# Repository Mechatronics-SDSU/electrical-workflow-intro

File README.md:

This system takes in an input A-F to change the brightness of an LED. This LED is also controlled by a button. When the button is pressed it turns the LED on, when the button is pressed again it turns the LED off. This is done on a high level by creating two circuits using an arduino and a breadboard, the button uses a pull-down resistor to guarantee a more precise output. After the button is pressed it switches the pin for the LED on which lights it up. On a low level, it uses the ATmega328P as a power supply and pin outputs, this goes through the tracks to interact with other parts of the board to function similarly to what was stated above.

The main challenges faced were learning how to create a proper schematic to make the PCB and learning how to create the basic circuit needed for the tinkercad simulation to run properly. I fixed most of this by finding guides online on what steps I needed to take to make it properly. This was overall a challenge but I learned a lot, the high level simulation works as expected and the PCB clears all design checks.

The parts used to make the board were a SPST button, an LED, an ATmega328P-A, two 10k ohm resistors, one 330 ohm resistor, the AVR-ISP-6, two capacitors, and a crystal.

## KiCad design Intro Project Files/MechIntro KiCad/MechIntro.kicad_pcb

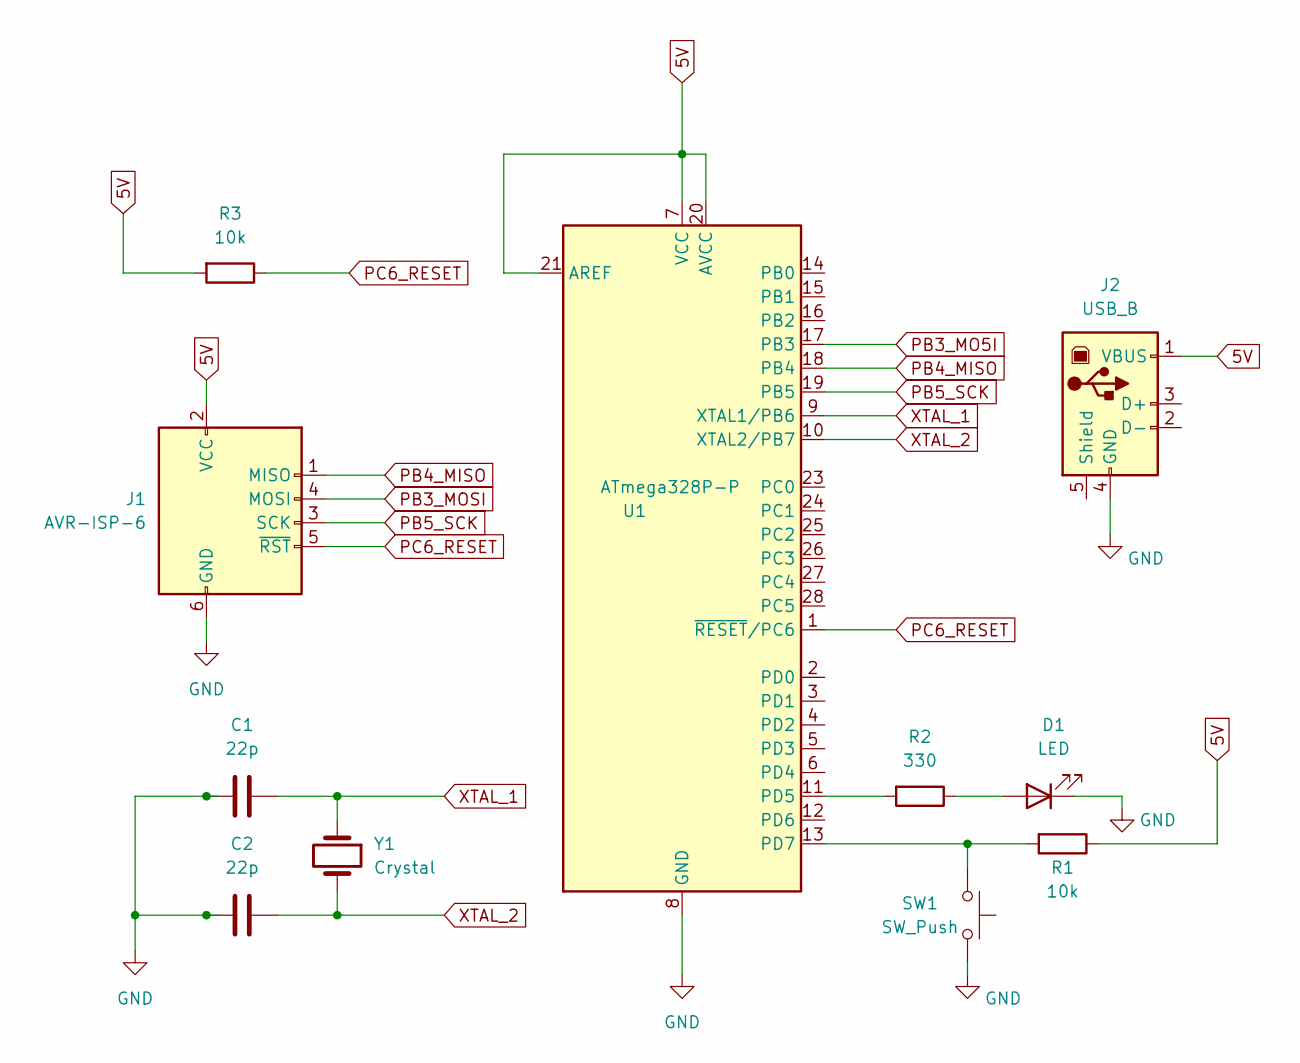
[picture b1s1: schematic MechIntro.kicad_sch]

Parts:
C1, C2: 22p; CP_Radial_D4.0mm_P2.00mm
D1: LED; LED_D3.0mm
J1: AVR-ISP-6; PinHeader_2x03_P1.27mm_Vertical
J2: USB_B; USB_B_OST_USB-B1HSxx_Horizontal
R1, R3: 10k; R_Axial_DIN0204_L3.6mm_D1.6mm_P7.62mm_Horizontal
R2: 330; R_Axial_DIN0204_L3.6mm_D1.6mm_P7.62mm_Horizontal
SW1: SW_Push; SW_PUSH_1P1T_6x3.5mm_H4.3_APEM_MJTP1243
U1: ATmega328P-P; DIP-28_W7.62mm
Y1: Crystal; Crystal_HC18-U_Vertical

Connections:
5V: J1.2 (VCC), J2.1 (VBUS), R1.1, R3.2, U1.7 (VCC), U1.20 (AVCC), U1.21 (AREF)
GND: C1.2, C2.2, D1.1 (K), J1.6 (GND), J2.4 (GND), SW1.2, U1.8 (GND), U1.22 (GND)
unnamed: D1.2 (A), R2.1
unnamed: R2.2, U1.11 (PD5)
unnamed: R1.2, SW1.1, U1.13 (PD7)
PB3_MO5I: U1.17 (PB3)
PB3_MOSI: J1.4 (MOSI)
PB4_MISO: J1.1 (MISO), U1.18 (PB4)
PB5_SCK: J1.3 (SCK), U1.19 (PB5)
PC6_RESET: J1.5 (~RST), R3.1, U1.1 (~RESET/PC6)
XTAL_1: C1.1, U1.9 (XTAL1/PB6), Y1.1
XTAL_2: C2.1, U1.10 (XTAL2/PB7), Y1.2

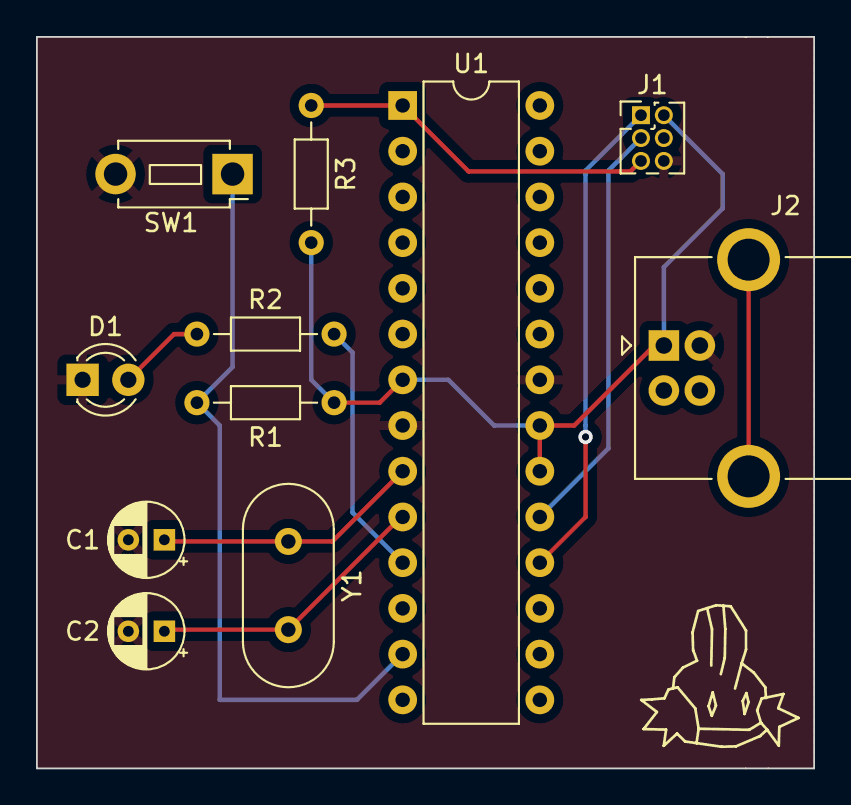
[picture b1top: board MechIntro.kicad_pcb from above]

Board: 2 copper layers, 43.2 x 40.6 mm, 11 parts (0 on the bottom side), 10 nets.

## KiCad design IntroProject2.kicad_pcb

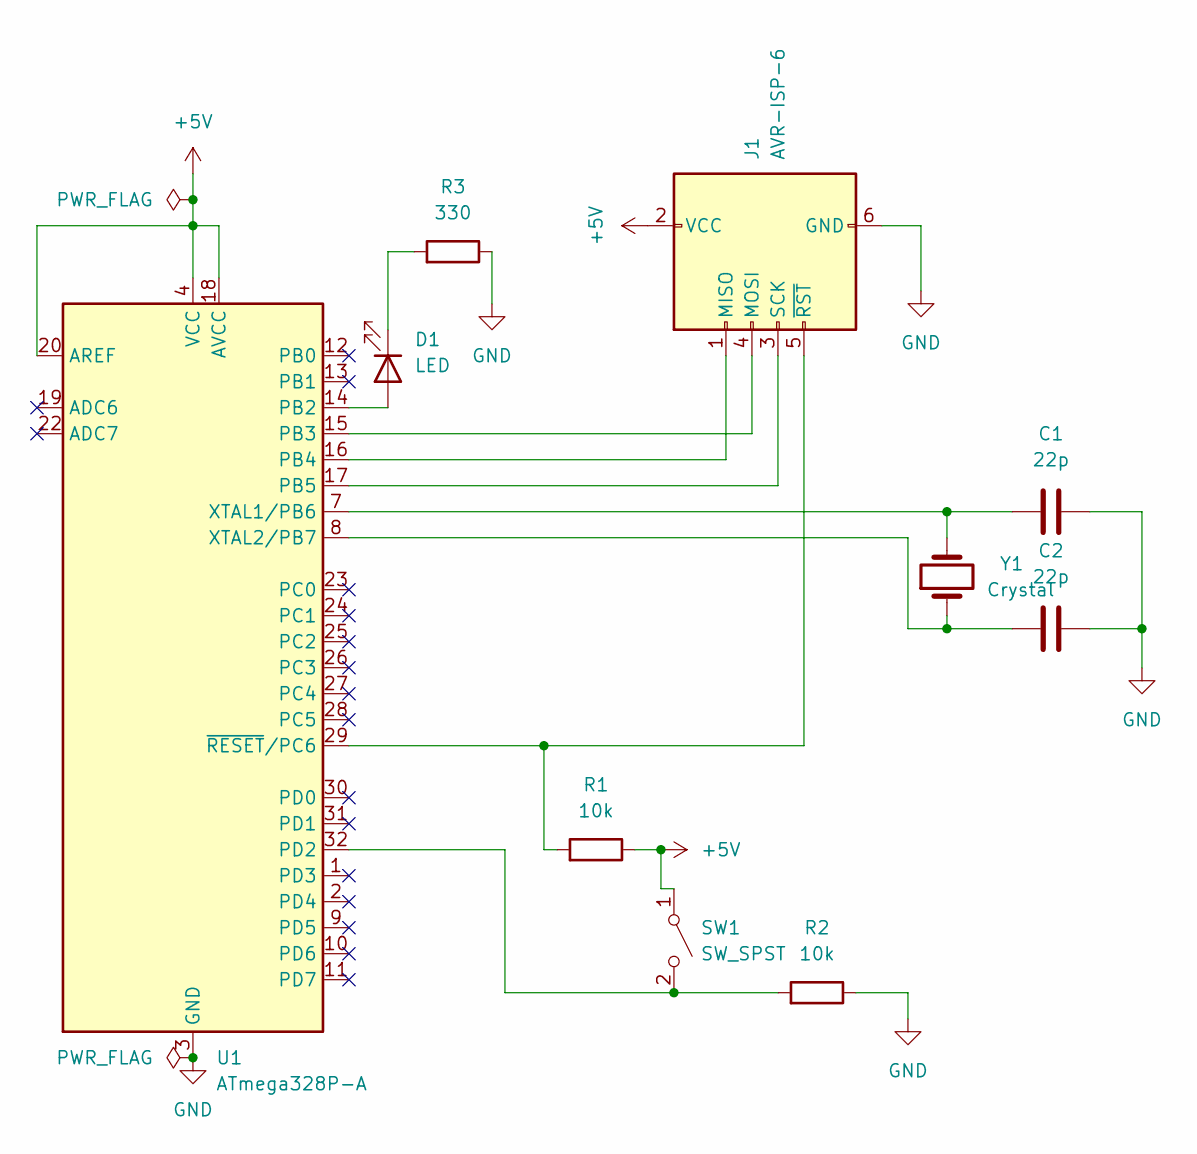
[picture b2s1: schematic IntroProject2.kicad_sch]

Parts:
C1, C2: 22p; C_1206_3216Metric
D1: LED; LED_0603_1608Metric
J1: AVR-ISP-6; PinHeader_1x06_P1.00mm_Vertical_SMD_Pin1Right
R1, R2: 10k; R_0603_1608Metric
R3: 330; R_0603_1608Metric
SW1: SW_SPST; SW_DIP_SPSTx01_Slide_6.7x4.1mm_W6.73mm_P2.54mm_LowProfile_J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
U1: ATmega328P-A; TQFP-32_7x7mm_P0.8mm
Y1: Crystal; Crystal_SMD_5032-2Pin_5.0x3.2mm

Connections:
+5V: J1.2 (VCC), R1.1, SW1.1 (A), U1.4 (VCC), U1.6 (VCC), U1.18 (AVCC), U1.20 (AREF)
GND: C1.2, C2.2, J1.6 (GND), R2.1, R3.1, U1.3 (GND), U1.5 (GND), U1.21 (GND)
unnamed: D1.2 (A), U1.14 (PB2)
unnamed: D1.1 (K), R3.2
unnamed: J1.1 (MISO), U1.16 (PB4)
unnamed: J1.4 (MOSI), U1.15 (PB3)
unnamed: J1.3 (SCK), U1.17 (PB5)
unnamed: J1.5 (~RST), R1.2, U1.29 (~RESET/PC6)
unnamed: R2.2, SW1.2 (B), U1.32 (PD2)
unnamed: C1.1, U1.7 (XTAL1/PB6), Y1.2
unnamed: C2.1, U1.8 (XTAL2/PB7), Y1.1

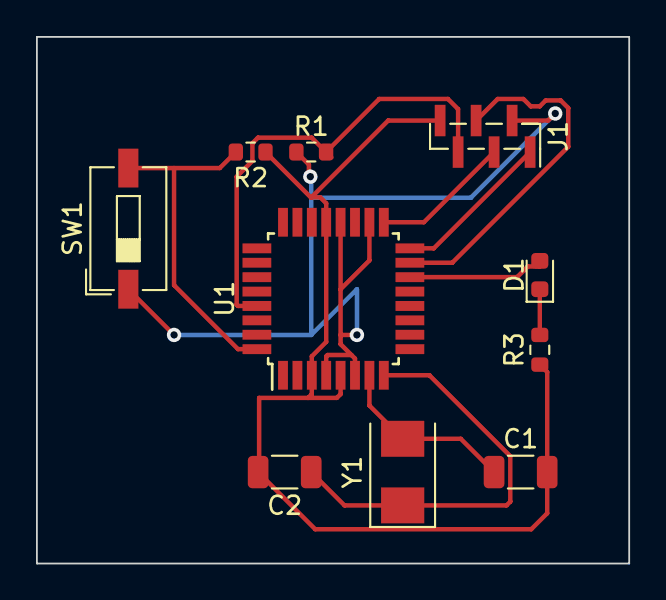
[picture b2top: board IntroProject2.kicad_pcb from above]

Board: 2 copper layers, 32.9 x 29.3 mm, 10 parts (0 on the bottom side), 11 nets.

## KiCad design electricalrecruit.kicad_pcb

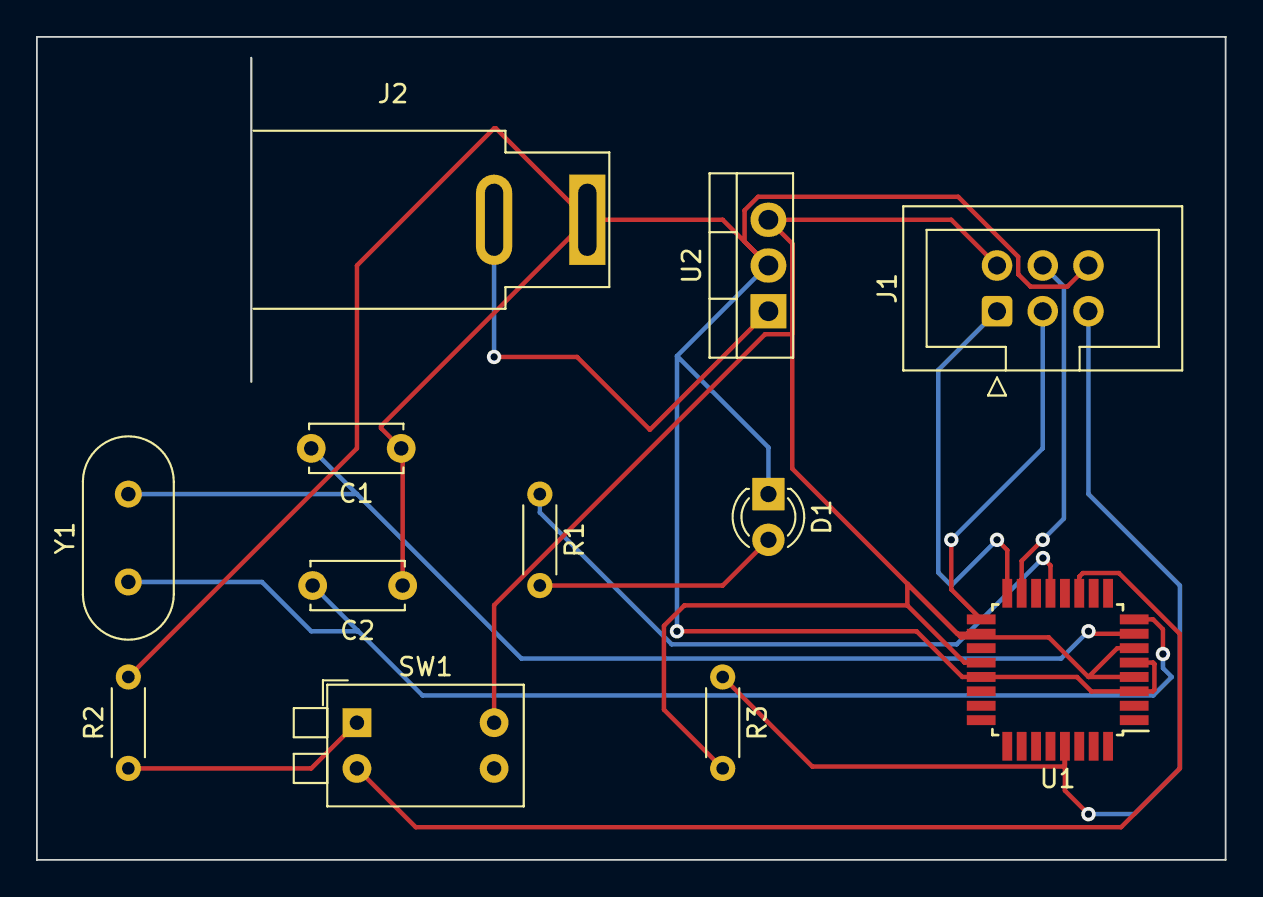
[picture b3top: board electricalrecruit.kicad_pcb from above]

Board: 2 copper layers, 66.0 x 45.7 mm, 12 parts (0 on the bottom side), 13 nets.

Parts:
C1, C2: 20pf; C_Disc_D5.0mm_W2.5mm_P5.00mm
D1: LED; LED_D3.0mm_Clear
J1: AVR-ISP-6; IDC-Header_2x03_P2.54mm_Vertical
J2: Barrel_Jack; BarrelJack_SwitchcraftConxall_RAPC10U_Horizontal
R1: 330; R_Axial_DIN0204_L3.6mm_D1.6mm_P5.08mm_Horizontal
R2, R3: 10k; R_Axial_DIN0204_L3.6mm_D1.6mm_P5.08mm_Horizontal
SW1: SW_MEC_5E; SW_DIP_SPSTx02_Piano_10.8x6.64mm_W7.62mm_P2.54mm
U1: ATmega328P-A; TQFP-32_7x7mm_P0.8mm
U2: L7805; TO-220-3_Vertical
Y1: 16Mhz Crystal; Crystal_HC49-U_Vertical

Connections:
+5V: J1.2 (VCC), R3.2, SW1.4 (A), U1.4 (VCC), U1.6 (VCC), U1.18 (AVCC), U1.20 (AREF), U2.3 (OUT)
DPIN_7: SW1.2, U1.11 (PD7)
GND: C1.1, C2.1, D1.1 (K), J1.6 (GND), J2.1, R2.2, U1.3 (GND), U1.5 (GND), U1.21 (GND), U2.2 (GND)
unnamed: J2.2, U2.1 (IN)
PB3_MOSI: J1.4 (MOSI), U1.15 (PB3)
PB4_MISO: J1.1 (MISO), U1.16 (PB4)
PB5_SCK: J1.3 (SCK), U1.17 (PB5)
PC6_RESET: J1.5 (~RST), R3.1, U1.29 (~RESET/PC6)
PWMPIN_9: R1.1, U1.13 (PB1)
R1: D1.2 (A), R1.2
SW1_PIN2GND: R2.1, SW1.1
XTAL_1: C1.2, U1.7 (XTAL1/PB6), Y1.2
XTAL_2: C2.2, U1.8 (XTAL2/PB7), Y1.1

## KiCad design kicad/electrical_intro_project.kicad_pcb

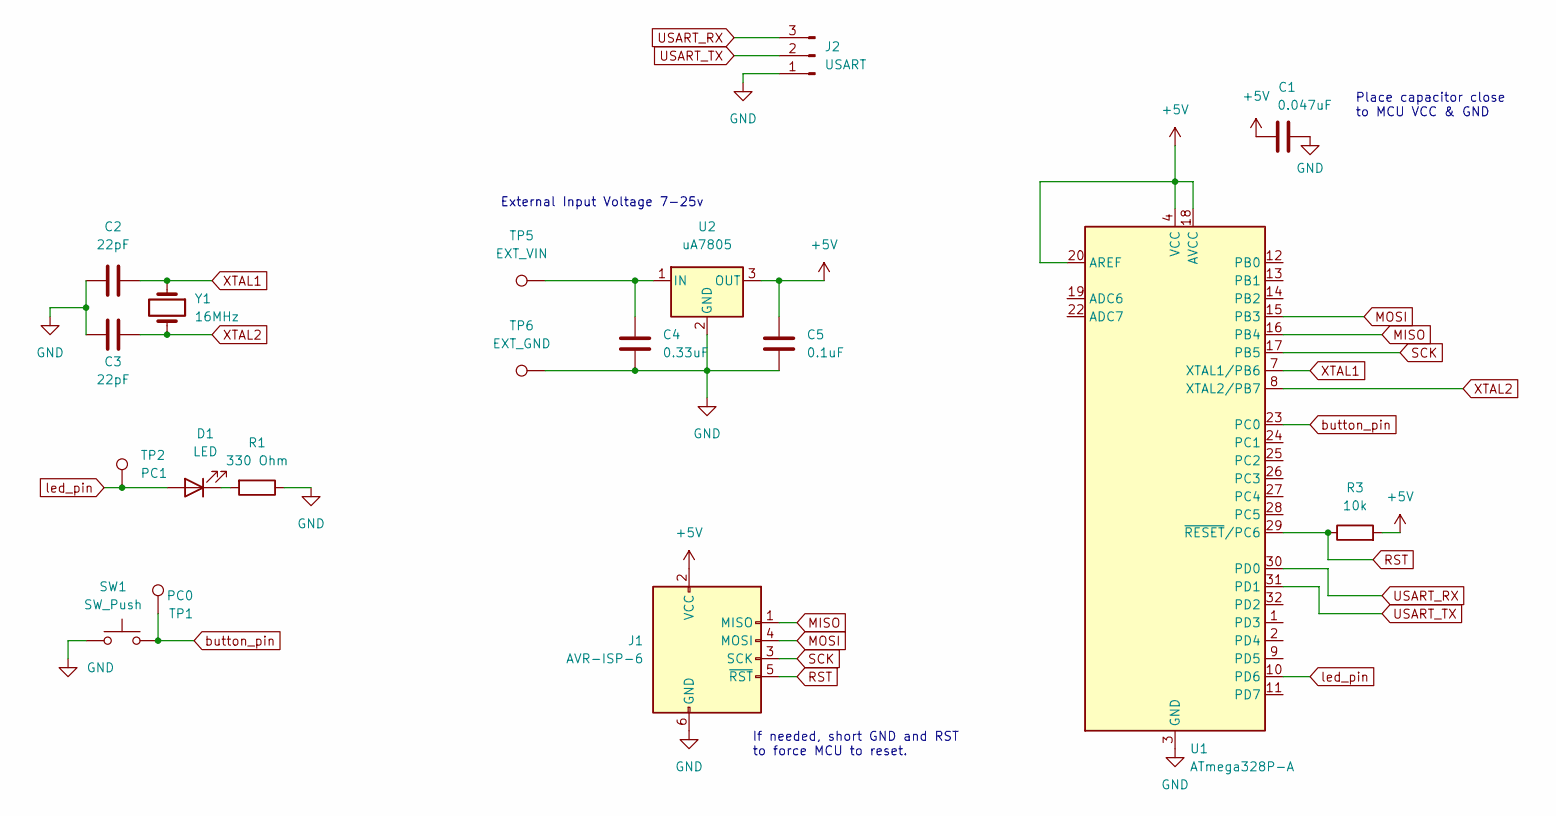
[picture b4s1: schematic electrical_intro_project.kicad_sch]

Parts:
C1: 0.047uF; C_0603_1608Metric_Pad1.08x0.95mm_HandSolder
C2, C3: 22pF; C_0603_1608Metric_Pad1.08x0.95mm_HandSolder
C4: 0.33uF; C_0603_1608Metric_Pad1.08x0.95mm_HandSolder
C5: 0.1uF; C_0603_1608Metric_Pad1.08x0.95mm_HandSolder
D1: LED; LED_1206_3216Metric_Pad1.42x1.75mm_HandSolder
J1: AVR-ISP-6; PinHeader_2x03_P2.54mm_Vertical
J2: USART; PinHeader_1x03_P2.54mm_Vertical
R1: 330 Ohm; R_0603_1608Metric_Pad0.98x0.95mm_HandSolder
R3: 10k; R_0603_1608Metric_Pad0.98x0.95mm_HandSolder
SW1: SW_Push; SW_PUSH_6mm_H7.3mm
TP1: PC0; TestPoint_Pad_1.0x1.0mm
TP2: PC1; TestPoint_Pad_1.0x1.0mm
TP5: EXT_VIN; TestPoint_Plated_Hole_D4.0mm
TP6: EXT_GND; TestPoint_Plated_Hole_D4.0mm
U1: ATmega328P-A; TQFP-32_7x7mm_P0.8mm
U2: uA7805; SOT-223
Y1: 16MHz; Crystal_HC49-4H_Vertical

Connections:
+5V: C1.1, C5.1, J1.2 (VCC), R3.2, U1.4 (VCC), U1.6 (VCC), U1.18 (AVCC), U1.20 (AREF), U2.3 (OUT)
GND: C1.2, C2.1, C3.2, C4.2, C5.2, J1.6 (GND), J2.1, R1.1, SW1.1, TP6.1, U1.3 (GND), U1.5 (GND), U1.21 (GND), U2.2 (GND)
MISO: J1.1 (MISO), U1.16 (PB4)
MOSI: J1.4 (MOSI), U1.15 (PB3)
unnamed: C4.1, TP5.1, U2.1 (IN)
unnamed: D1.1 (K), R1.2
RST: J1.5 (~RST), R3.1, U1.29 (~RESET/PC6)
SCK: J1.3 (SCK), U1.17 (PB5)
USART_RX: J2.3, U1.30 (PD0)
USART_TX: J2.2, U1.31 (PD1)
XTAL1: C2.2, U1.7 (XTAL1/PB6), Y1.1
XTAL2: C3.1, U1.8 (XTAL2/PB7), Y1.2
button_pin: SW1.2, TP1.1, U1.23 (PC0)
led_pin: D1.2 (A), TP2.1, U1.10 (PD6)

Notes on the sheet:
External Input Voltage 7-25v
Place capacitor close to MCU VCC & GND
If needed, short GND and RST to force MCU to reset.

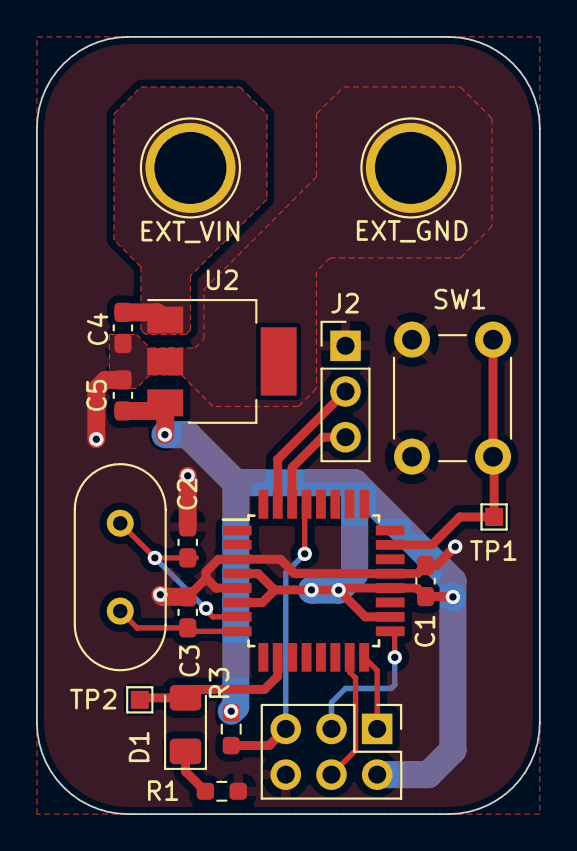
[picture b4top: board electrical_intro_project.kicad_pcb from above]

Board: 2 copper layers, 27.9 x 43.2 mm, 18 parts (0 on the bottom side), 14 nets.

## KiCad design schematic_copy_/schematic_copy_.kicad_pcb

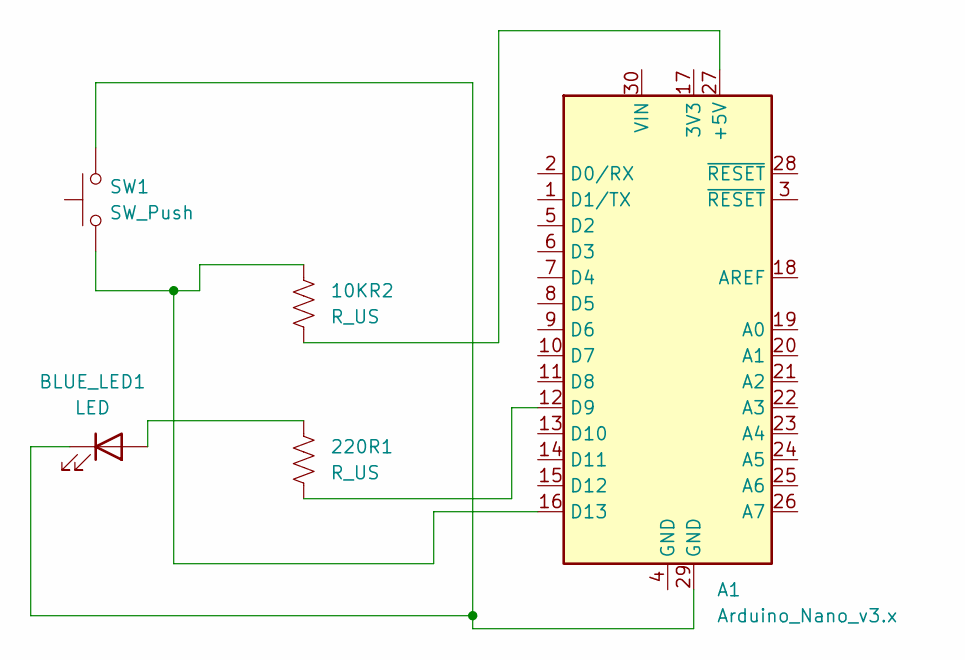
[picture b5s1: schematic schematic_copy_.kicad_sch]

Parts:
10KR2, 220R1: R_US; R_Axial_DIN0204_L3.6mm_D1.6mm_P5.08mm_Horizontal
A1: Arduino_Nano_v3.x; Arduino_Nano
BLUE_LED1: LED; LED_D3.0mm
SW1: SW_Push; SW_PUSH_6mm

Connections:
unnamed: 10KR2.2, A1.27 (+5V)
unnamed: 220R1.2, A1.12 (D9)
unnamed: 10KR2.1, A1.16 (D13), SW1.1
unnamed: 220R1.1, BLUE_LED1.2 (A)
unnamed: A1.29 (GND), BLUE_LED1.1 (K), SW1.2

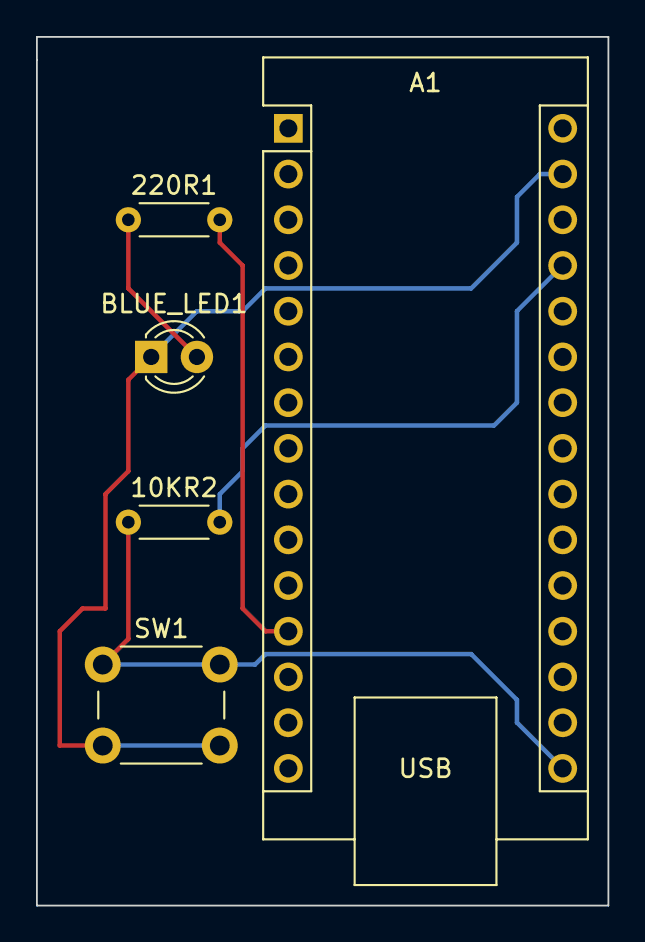
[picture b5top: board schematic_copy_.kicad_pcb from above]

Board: 2 copper layers, 31.8 x 48.3 mm, 5 parts (0 on the bottom side), 5 nets.

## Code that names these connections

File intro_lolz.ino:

#define LED_PIN 1                                    // PB1
#define BUTTON_PIN 2                                 // PD2
#define topVal 255 
#define rangeOduty 5 

volatile uint8_t lumen = 0;                           //global for duty cycle adj
volatile uint8_t pressCount = 0;                      //global for truth of state 
char pressed[]= ("Pressed b*tch \n");                 //it'n that fun

void usartSet();                                      //prototypes
void gpioSet();
void timer1Set();
void boostDown(char* input);
void fadeLed(uint8_t targetValue);
void uart_transmit (char data); 
void report();                                         //end prototypes

void setup()                                           //initializing launch
{
  
usartSet();      
gpioSet();                  
timer1Set();

}


void loop()                                             //do the stuff
{
  
  if (UCSR0A & (1<<RXC0))                               //if ready to read
  { 
    
    char inChar = UDR0;                                 //read character

    boostDown(&inChar);                                 //lower to upper if needed

    if (inChar >= 'A' && inChar <= 'F')                 //if valid option
    {
                                                        //if character is alphabet
      uint8_t delta =  (inChar - 'A');                  //where u r - where u been
      uint8_t sectional=topVal / rangeOduty;            //a 5th of 255
      uint8_t destLumen = delta*sectional;              //n sectionals

      fadeLed(destLumen);                               //send it to fade
    } 
    
    else if (inChar == '?')                             //select report case
    {
     report();            
    }
    
    else if (inChar == '\n'){}                      
    
    else{
    Serial.println("Not a valid option");               //I got lazy here not
                                                        //at this spec pnt tho
    }                                                
  }
}


void uart_transmit (char data) 
{
  while (!( UCSR0A & (1<<UDRE0)));                      //w8 while not empty b4 read;                               
  UDR0 = data;                                          //write the data in register
}


void usartSet()
{
  UBRR0H = 0;
  UBRR0L = 8;  
  
  UCSR0B = (1<<RXEN0) | 
           (1<<TXEN0);                                  //enable reciever transm
           
  UCSR0C = (1<<UCSZ01) |
           (1<<UCSZ00);                                 //for 8-bit char size
}


void gpioSet()
{
  DDRB |= (1 << LED_PIN);                               //PB1 D9 LED Pin
  DDRD &= ~(1 << BUTTON_PIN);                           //PD2 D2 Push button read
  PORTD |= (1 << BUTTON_PIN);                           //pull-up config
}


void timer1Set()
{                            
  TCCR1A |= (1 << COM1A1);                              //Com settings
  TCCR1A &= ~(1 << COM1A0);                             //non-inverting

  TCCR1A &= ~(1 << WGM10);                              //Fast PWM
  TCCR1A |= (1 << WGM11);           
  TCCR1B |= (1 << WGM13) |
            (1 << WGM12);
           
  TCCR1B |= (1<<CS10);                                  //no p.s. lolz

  PCICR  |= (1 << PCIE2);                               //enable interrupt
  PCMSK2 |= (1 << PCINT18);                             //Msk for PD2
 
  ICR1 = topVal;                                        //cuz I know Joe loves
  OCR1A = 0;                                            //duty cycle action
}


void boostDown(char* input)
{     
  if (*input >= 'a' && *input <= 'z')                   //if lower case, 
                                                        //then to upper
      { 
        *input -= (1<<5);                               //difference of 32
      }                                                 //ref to char addy
}


void fadeLed(uint8_t targetValue) 
{
  while (OCR1A != targetValue)                          //while not satisfied
  {
    if (OCR1A < targetValue)                            //if not enough
    {
      OCR1A++;                                          //drink more seed
    } 
    else 
    {
      OCR1A--;                                          //ralph some seed
    }

    delay(10);                                          //drink seed responsibly
  }
  
  lumen = OCR1A;                                        //Global store seed level
}                                                       //1st rule don't talk about
                                                        //seed club


void report()                                           //I'll just apologize now for this function
{                                                       //and would appreciate light judgment zzz
      char report [] = ("The brightness is "); 
      char precentile = (2*(lumen/(topVal/5)))+ '0';    //0-100% in 20 int
      if(precentile == ':')                             //ps i'm illiterate
      precentile = '1';
      char precSym = '%';
      int i = 0;

         while(report[i] != '\0')                       //tx till null
        {
           uart_transmit ( report[i]); 
           i++;
        }
        
      if (!(pressCount & 1))                             //if not even press is odd
      {
        uart_transmit ( precentile);
        if (precentile == '1')                          //idea is 1 is only 100 on char rep
          {
          uart_transmit ( '0');                         //cheap af
          }
        if (precentile > '0')                           
          {
          uart_transmit ( '0');                         //always 0 present
          }
      }   
        else
      uart_transmit ( '0');                             //def just 0... cuz zzz
      uart_transmit ( precSym);                         //cheap but my attn espenzive
      uart_transmit ( '\n');
  
}


ISR(PCINT2_vect) 
{
  int i = 0;
     
     cli();                                             //disable global interrupts
     delay(5000);                                       //w8 a dickens
  if (!(PIND & (1 << BUTTON_PIN)))                      //if butt pressed = 0
  {  
    if (pressCount & 1)                                 //if pressed odd
    {
      while(OCR1A != lumen)                             //Restore the brightness
      {
      OCR1A++;
      delay(500);                                       //do this at a controlled rate
      }
    } 
    
    else                                                //if pressed even.. good like
    {  
      while(OCR1A != 0)
      {
      OCR1A--;                                          //Turn off the LED, close door
      delay(500);
      }
    }
    
   while(pressed[i]!= '\0')                             //again why uart proto here vs funct?
   {                                                    //cause lazy idk mb mb
    uart_transmit (pressed[i]);
    i++; 
   }
     pressCount++;                                      //Increment the press count
     delay(5000);                                       //drink seed responsibly
  }
  delay(5000);                                          //be sure
  sei();                                                //enable global interrupts
}

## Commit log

2023-02-18 Create ledWithButtonFinal.ino
    Tye Williams Recruit Project
2023-02-18 Felix Monasterio Intro Project
2023-02-21 Intro Project
2023-05-16 Added everything to my branch
2023-08-21 Images and Code for Intro Project
2023-08-21 My drafted bio
2023-08-21 Adding KiCAD and Gerber files
2023-09-05 Upload intro project
2023-09-09 well... coulda been worse
2023-09-17 Create mechatronics_fall_2023_intro_project1.ino
    Programmed Arduino to turn LED on using a push button, added adjustable brightness using inputs to Serial Terminal.
2023-09-17 Publishing PCB schematic, PCB, GBR, and DRL files to branch. Updating README.md.
    Publishing PCB schematic, PCB, GBR, and DRL files to branch. Updating README.md.
2023-09-18 Intro Submission
    Submitting all files for Fall 2023 Intro Project
2023-09-22 Text file for recruit project
2023-09-22 Arduino code for recruit project. 10 states, on off
2023-09-22 IntroProject
2023-09-23 Delete arduinoRecruit.c
    I have no idea why this was in my branch, but this is not my code which is why I am deleting it.
2023-09-23 Delete ray.txt
    This is not my .txt and I have no idea why it is in my branch which is why i am deleting it.
2023-10-10 Uploaded .ino & README
2023-10-27 Intro Project Files
